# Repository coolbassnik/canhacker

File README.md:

# canhacker
KiCAD pcb for CanHacker

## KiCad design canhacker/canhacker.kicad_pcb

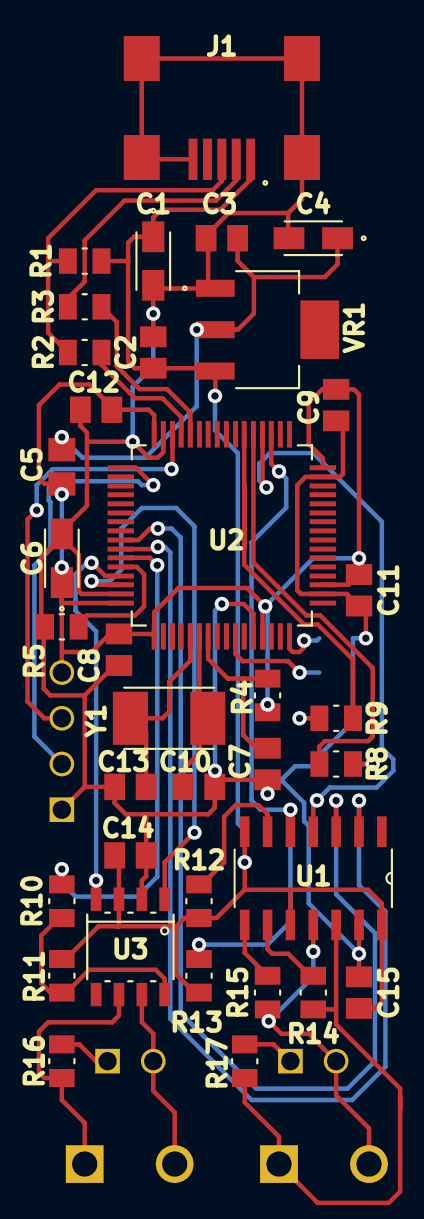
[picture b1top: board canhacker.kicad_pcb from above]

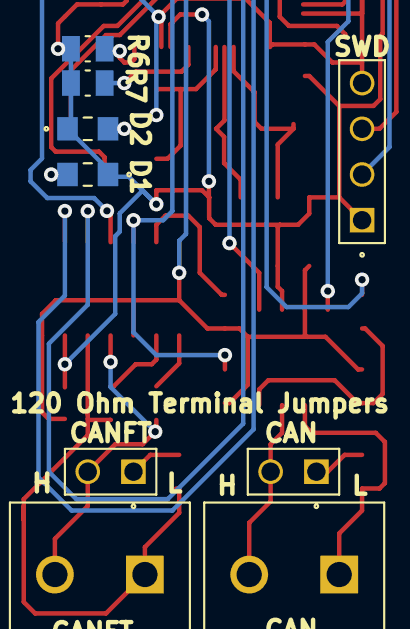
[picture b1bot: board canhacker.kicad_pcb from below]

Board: 2 copper layers, 45 parts (9 on the bottom side), 37 nets.

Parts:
C1, C4, C6: 10uF; CAPMP3216X180N
C2, C3, C7, C8, C9, C11, C12, C14, C15: 100nF; CAPC2012X88N
C5: BEAD; CAPC2012X135N
C10, C13: 18pF; CAPC2012X88N
CAN: JUMPER; SAMTEC_MTSW-101-09-S-D-530
CAN#2: CAN; CUI_TB003-500-P02BE
CANFT: JUMPER; SAMTEC_MTSW-101-09-S-D-530
CANFT#2: CANFT; CUI_TB003-500-P02BE
D1: RED; LED_7012X1
D2: GREEN; LED_7012X1
J1: Micro USB; GCT_USB2066-05-RBHM-XX-STB-00-00-A_REVD
R1: 1K5; RESC2012X65N
R2, R3: 22R; RESC2012X65N
R4: 100K; RESC2012X65N
R5: 220R; RESC2012X65N
R6, R7: JUMPER; RESC2012X65N
R8, R9: 1K; RESC2012X65N
R10: 100R; RESC2012X65N
R11, R12, R13: 10K; RESC2012X65N
R14, R15: 4K7; RESC2012X65N
R16, R17: 120R; RESC2012X65N
SWD: TSW-104-24-G-S; SAMTEC_TSW-104-24-G-S
U1: TJA1055T_C,512; SOIC127P600X175-14N
U2: STM32F105RBT6; QFP50P1200X1200X160-64N
U3: TJA1051T_3; SOT96-1
VR1: LM1117MPX-3.3; VREG_LM1117MPX-3.3
Y1: 8.000 Mhz; XTAL500X320X130N

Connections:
+3V3: C5.2, C6.1, C8.1, C9.1, C11.1, C12.1, R4.2, SWD.04, U2.1, U2.13, U2.19, U2.32, U2.48, U2.64
+5V: C1.1, C2.1, C14.1, C15.1, J1.1, R1.2, R11.2, R12.2, R13.2, U1.7, U1.10, U1.14, U3.3, VR1.3
CAN2ERR: U1.4, U2.36
CAN2RX: U1.3, U2.57
CAN2STB: R13.1, U1.5, U2.35
CAN2TX: U1.2, U2.58
GND: C1.2, C2.2, C3.2, C4.2, C6.2, C7.2, C8.2, C9.2, C10.2, C11.2, C12.2, C13.2, C14.2, C15.2, D1.C, D2.C, J1.5, J1.6, J1.7, J1.8, J1.9, R5.1, R6.1, R7.2, SWD.01, U1.13, U2.12, U2.18, U2.31, U2.47, U2.63, U3.2, VR1.1
unnamed: C3.1, C4.1, C5.1, VR1.2
unnamed: C7.1, R4.1, U2.7
unnamed: C13.1, U2.5, Y1.1
unnamed: D1.A, R8.2
unnamed: D2.A, R9.2
unnamed: J1.2, R3.1
unnamed: J1.3, R1.1, R2.1
unnamed: CAN#2.1, R16.1, U3.6
unnamed: CAN.02, CAN#2.2, U3.7
unnamed: CANFT#2.1, R14.1, R17.1, U1.12
unnamed: CANFT.02, CANFT#2.2, R15.1, U1.11
unnamed: CAN.01, R16.2
unnamed: CANFT.01, R17.2
unnamed: R2.2, U2.45
unnamed: R3.2, U2.44
unnamed: R5.2, U2.60
unnamed: R6.2, U2.16
unnamed: R7.1, U2.10
unnamed: R8.1, U2.37
unnamed: R9.1, U2.38
unnamed: R10.1, U2.59
unnamed: R10.2, R11.1, U3.8
unnamed: R12.1, U1.6
unnamed: R14.2, U1.9
unnamed: R15.2, U1.8
unnamed: U2.61, U3.4
unnamed: U2.62, U3.1
OSC: C10.1, U2.6, Y1.2
SWC: SWD.02, U2.49
SWD: SWD.03, U2.46

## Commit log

2021-11-12 First fabrication 10pcs
